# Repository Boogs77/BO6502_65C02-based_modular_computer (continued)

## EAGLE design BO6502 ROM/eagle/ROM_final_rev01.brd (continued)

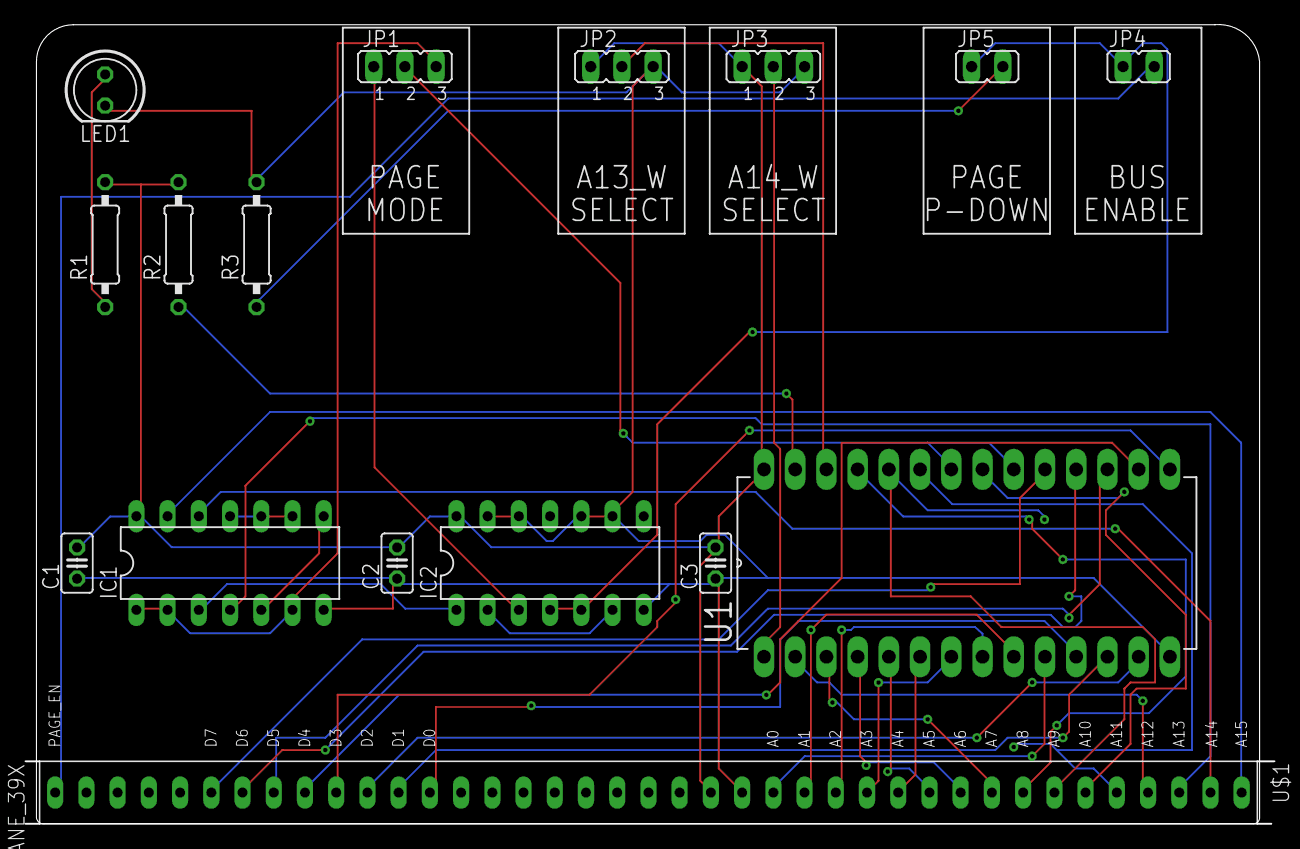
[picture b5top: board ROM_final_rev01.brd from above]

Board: 2 copper layers, 101.6 x 65.0 mm, 16 parts (0 on the bottom side), 40 nets.

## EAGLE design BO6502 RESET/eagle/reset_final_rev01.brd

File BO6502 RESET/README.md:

# BO6502 Reset & Clock Module

The **Reset & Clock Module** is a critical system utility for the BO6502. It provides a reliable power-on reset pulse and a flexible clock generation system to adapt the CPU speed to different hardware requirements.

---

## 🛠 Hardware Specifications

This module combines two essential system functions: power management and timing.

### Reset Circuitry
* **Logic:** Built around the classic **NE555** timer configured in monostable mode.
* **Function:** Ensures a clean and stable active-low RESET pulse upon power-up or manual trigger, ensuring the 65C02 CPU and peripherals initialize correctly.

### Clock Management & Scaling
The board features a flexible clock distribution system, allowing the user to select between different frequencies using a **74LS74** dual flip-flop for frequency division.

* **Direct 2 MHz Clock:** The system can be driven directly by a 2 MHz source (Note: the onboard clock on the CPU module must be disabled when using this configuration).
* **Scaled Frequencies:** Using the 7474 divider, the module can provide:
    * **1 MHz** (Division by 2).
    * **500 kHz** (Further division).
* **Selection:** This allows for high-speed operation or lower speeds for debugging and compatibility with older peripherals.

---

## 🕹️ Integration & Configuration

To use the external clock from this module, ensure the clock jumper/oscillator on the **BO6502 CPU Module** is disconnected to avoid bus contention.

| Frequency | Source / Logic | Recommended Use |
| :--- | :--- | :--- |
| **2 MHz** | Direct Bypass | Standard high-speed operation |
| **1 MHz** | 7474 Divider (Q1) | Standard 6502 compatibility |
| **500 kHz** | 7474 Divider (Q2) | Debugging / Slow peripheral testing |

---

## 📐 Board Layout & Rendering

The layout provides easy access to the reset button and features jumpers for quick frequency switching.

---

## 📂 Related Modules
* 🧠 **[CPU Module](https://github.com/Boogs77/BO6502/blob/main/BO6502%20CPU/README.md)**: W65C02 central processor (requires clock coordination).
* 🏗️ **[Backplate System](https://github.com/Boogs77/BO6502/blob/main/BO6502%20BACKPLATE/README.md)**: Distributes the Reset and Clock signals to all slots.
* 🖥️ **[Monitor Interface](https://github.com/Boogs77/BO6502/blob/main/BO6502%20MONITOR/README.md)**: Used to verify bus activity after a reset.

---

## 🏭 Gerber files

Ready for PCB manufacturing (2 layers, drill file included). The drill hits of each file have been checked against its EAGLE board.

| Gerber (ZIP) | Exported from |
| :--- | :--- |
| [`BO6502_reset_gerber.zip`](export/BO6502_reset_gerber.zip) | `reset_final_rev01.brd` |

---
© 2026 Boogs77 | BO6502 Project - Technical Documentation.

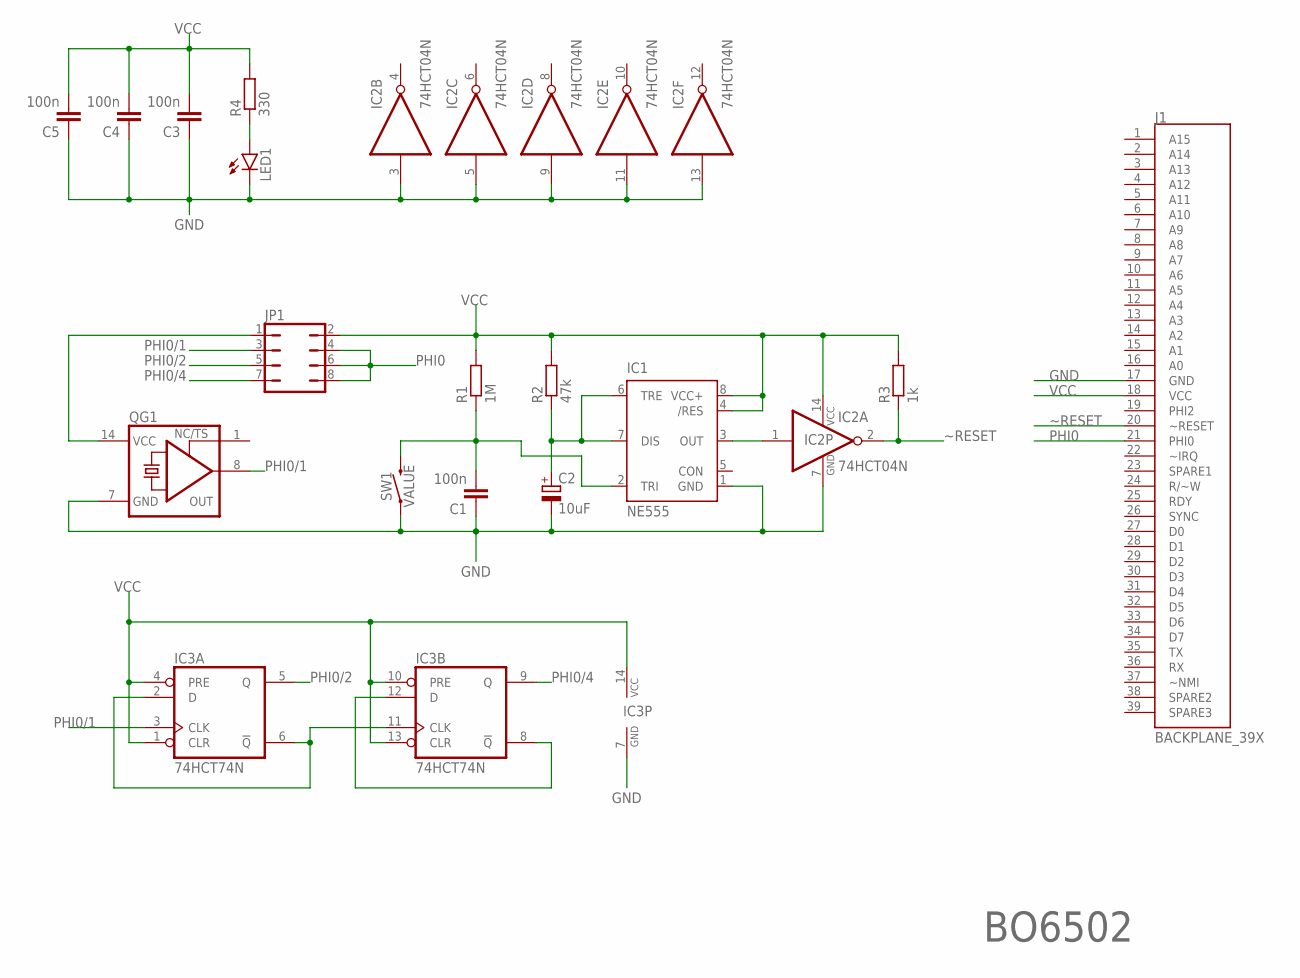
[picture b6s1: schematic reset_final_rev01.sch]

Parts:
C1, C3, C4, C5: 100n; C025-025X050
C2: 10uF; B45181A
IC1: NE555; DIL-08
IC2: 74HCT04N; DIL14
IC3: 74HCT74N; DIL14
J1: BACKPLANE_39X; BP_39X
JP1: JP4Q
LED1: LED5MM
QG1: XO-14; DIL14S
R1: 1M; 0207/10
R2: 47k; 0207/10
R3: 1k; 0207/10
R4: 330; 0207/10
SW1: MOMENTARY-SWITCH-SPST-PTH-6.0MM-KIT; TACTILE_SWITCH_PTH_6.0MM_KIT

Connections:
GND: C1.1, C2.-, C3.1, C4.1, C5.1, IC1.1 (GND), IC2.3 (I), IC2.5 (I), IC2.7 (GND), IC2.9 (I), IC2.11 (I), IC2.13 (I), IC3.7 (GND), J1.17 (GND), LED1.K (C), QG1.7 (GND), SW1.1
unnamed: JP1.1, QG1.14 (VCC)
unnamed: IC1.3 (OUT), IC2.1 (I)
unnamed: C2.+, IC1.6 (TRE), IC1.7 (DIS), R2.1
unnamed: C1.2, IC1.2 (TRI), R1.1, SW1.3 (2)
unnamed: LED1.A, R4.1
unnamed: IC3.2 (D), IC3.6 (!Q), IC3.11 (CLK)
unnamed: IC3.8 (!Q), IC3.12 (D)
PHI0: J1.21 (PHI0), JP1.4, JP1.6, JP1.8
PHI0/1: IC3.3 (CLK), JP1.3, QG1.8 (OUT)
PHI0/2: IC3.5 (Q), JP1.5
PHI0/4: IC3.9 (Q), JP1.7
VCC: C3.2, C4.2, C5.2, IC1.4 (/RES), IC1.8 (VCC+), IC2.14 (VCC), IC3.1 (CLR), IC3.4 (PRE), IC3.10 (PRE), IC3.13 (CLR), IC3.14 (VCC), J1.18 (VCC), JP1.2, R1.2, R2.2, R3.2, R4.2
~RESET: IC2.2 (O), J1.20 (~RESET), R3.1

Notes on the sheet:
BO6502

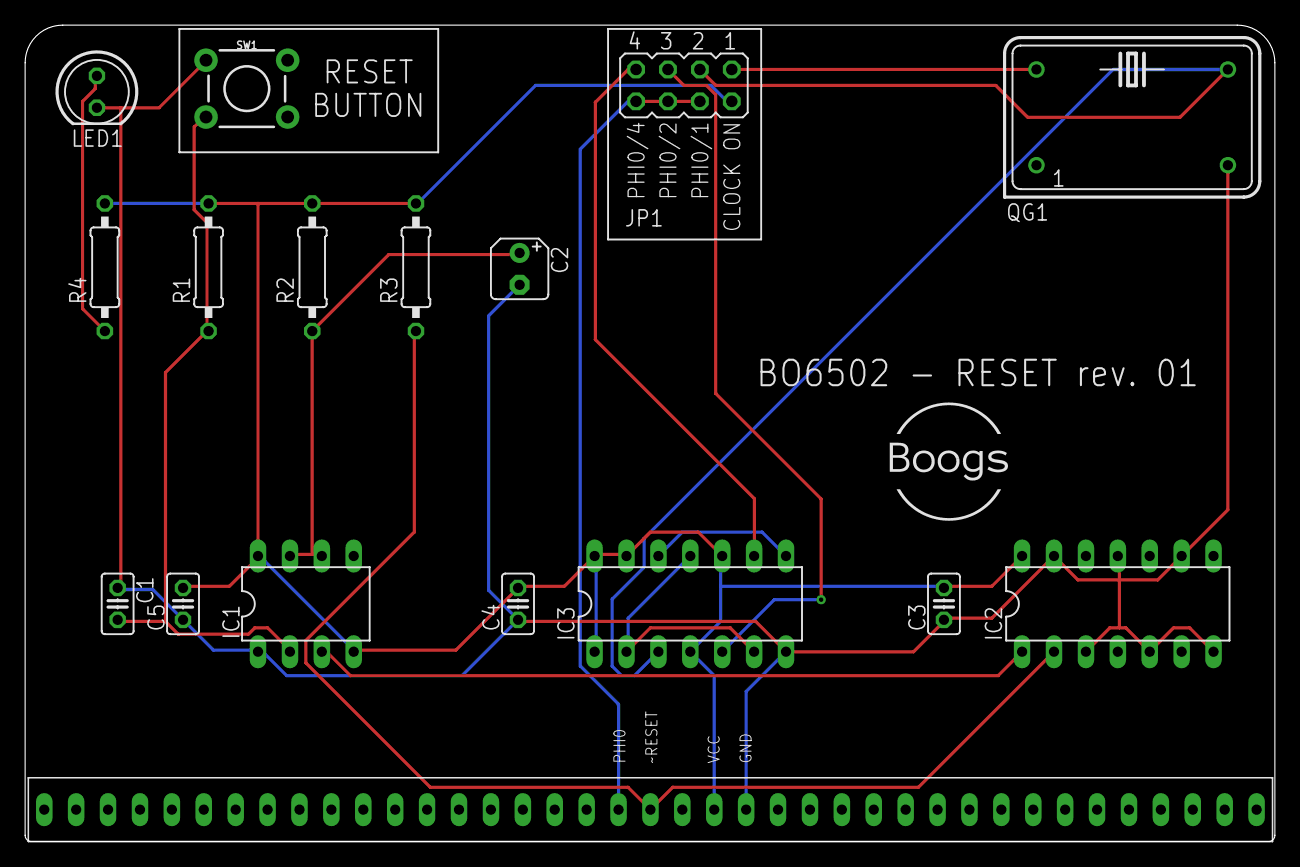
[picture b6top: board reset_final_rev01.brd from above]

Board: 2 copper layers, 99.5 x 65.0 mm, 17 parts (0 on the bottom side), 14 nets.

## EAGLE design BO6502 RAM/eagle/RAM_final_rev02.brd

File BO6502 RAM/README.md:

# BO6502 RAM Module

The **RAM Module** provides the primary volatile memory storage for the BO6502 system. This revision features a highly flexible addressing logic, allowing the user to map or exclude specific memory banks through a series of onboard jumpers.

---

## 🛠 Hardware Specifications

The module is designed to interface with the 6502 bus, providing fast access to 32KB of static RAM (SRAM).

* **Base Addressing:** By default, the module is mapped to the **$0000 - $7FFF** range. This is achieved by connecting the **A15** address line to the Enable pin of the decoder logic (active when A15 is Low).
* **Clock Synchronization:** The module typically triggers with the system clock to ensure data integrity during R/W cycles. However, **JP4** allows the user to set **IC2** as "Always Enabled," bypassing the system clock trigger for specific hardware configurations.

---

## 🕹️ Jumper Configuration & Memory Mapping

This module stands out for its versatility, managed through several jumper sets:

### I/O Exclusion Jumpers
The board includes **8 dedicated jumpers** designed to "carve out" space within the $0000 - $7FFF range. This allows other peripherals (such as I/O modules) to reside in that memory space without causing bus contention with the RAM.

### Address Bank Management
* **JP1 & JP2:** These jumpers allow the physical disconnection of **A13** and **A14** lines, useful for testing or specific memory mirroring configurations.
* **High-Memory Toggle:** A specific jumper configuration allows the RAM to be remapped to the **$8000 - $FFFF** range (High Memory) instead of its default Low Memory position.

---

## 📐 Board Layout & Rendering

The Revision 02 layout features optimized traces for high-speed signal integrity and clearly labeled jumper blocks for easy configuration.

---

## 📂 Related Modules
* 🏗️ **[Backplate System](https://github.com/Boogs77/BO6502/blob/main/BO6502%20BACKPLATE/README.md)**: 39-pin system bus connection.
* 🧠 **[CPU Module](https://github.com/Boogs77/BO6502/blob/main/BO6502%20CPU/README.md)**: W65C02 central processor.
* 🖥️ **[Monitor Interface](https://github.com/Boogs77/BO6502/blob/main/BO6502%20MONITOR/README.md)**: Recommended for debugging RAM read/write operations.

---

## 🏭 Gerber files

Ready for PCB manufacturing (2 layers, drill file included). The drill hits of each file have been checked against its EAGLE board.

| Gerber (ZIP) | Exported from |
| :--- | :--- |
| [`BO6502-RAM_gerber.zip`](export/BO6502-RAM_gerber.zip) | `RAM_final_rev02.brd` |

---
© 2026 Boogs77 | BO6502 Project - Technical Documentation.

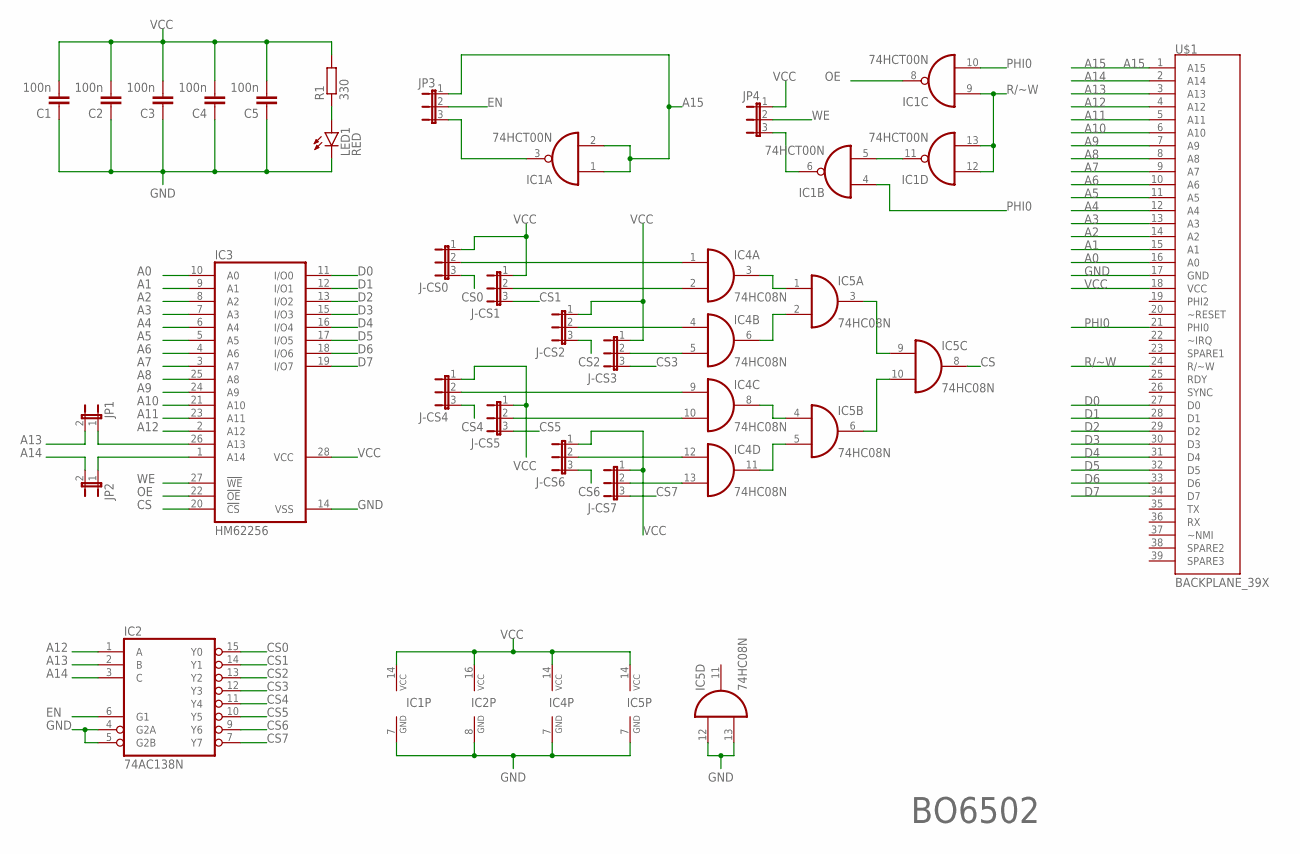
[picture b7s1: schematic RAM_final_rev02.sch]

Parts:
C1, C2, C3, C4, C5: 100n; C025-025X050
IC1: 74HCT00N; DIL14
IC2: 74AC138N; DIL16
IC3: HM62256; DIL28-6
IC4, IC5: 74HC08N; DIL14
J-CS0: J-CS0; JP2
J-CS1: J-CS1; JP2
J-CS2: J-CS2; JP2
J-CS3: J-CS3; JP2
J-CS4: J-CS4; JP2
J-CS5: J-CS5; JP2
J-CS6: J-CS6; JP2
J-CS7: J-CS7; JP2
JP1: JP1
JP2: JP2; JP1
JP3: JP3; JP2
JP4: JP4; JP2
LED1: RED; LED5MM
R1: 330; 0207/10
U$1: BACKPLANE_39X; BP_39X

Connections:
A0: IC3.10 (A0), U$1.16 (A0)
A1: IC3.9 (A1), U$1.15 (A1)
A2: IC3.8 (A2), U$1.14 (A2)
A3: IC3.7 (A3), U$1.13 (A3)
A4: IC3.6 (A4), U$1.12 (A4)
A5: IC3.5 (A5), U$1.11 (A5)
A6: IC3.4 (A6), U$1.10 (A6)
A7: IC3.3 (A7), U$1.9 (A7)
A8: IC3.25 (A8), U$1.8 (A8)
A9: IC3.24 (A9), U$1.7 (A9)
A10: IC3.21 (A10), U$1.6 (A10)
A11: IC3.23 (A11), U$1.5 (A11)
A12: IC2.1 (A), IC3.2 (A12), U$1.4 (A12)
A13: IC2.2 (B), JP1.2, U$1.3 (A13)
A14: IC2.3 (C), JP2.2, U$1.2 (A14)
A15: IC1.1 (I0), IC1.2 (I1), JP3.1, U$1.1 (A15)
CS: IC3.20 (!CS), IC5.8 (O)
CS0: IC2.15 (Y0), J-CS0.3
CS1: IC2.14 (Y1), J-CS1.3
CS2: IC2.13 (Y2), J-CS2.3
CS3: IC2.12 (Y3), J-CS3.3
CS4: IC2.11 (Y4), J-CS4.3
CS5: IC2.10 (Y5), J-CS5.3
CS6: IC2.9 (Y6), J-CS6.3
CS7: IC2.7 (Y7), J-CS7.3
D0: IC3.11 (I/O0), U$1.27 (D0)
D1: IC3.12 (I/O1), U$1.28 (D1)
D2: IC3.13 (I/O2), U$1.29 (D2)
D3: IC3.15 (I/O3), U$1.30 (D3)
D4: IC3.16 (I/O4), U$1.31 (D4)
D5: IC3.17 (I/O5), U$1.32 (D5)
D6: IC3.18 (I/O6), U$1.33 (D6)
D7: IC3.19 (I/O7), U$1.34 (D7)
EN: IC2.6 (G1), JP3.2
GND: C1.1, C2.1, C3.1, C4.1, C5.1, IC1.7 (GND), IC2.4 (G2A), IC2.5 (G2B), IC2.8 (GND), IC3.14 (VSS), IC4.7 (GND), IC5.7 (GND), IC5.12 (I0), IC5.13 (I1), LED1.K (C), U$1.17 (GND)
unnamed: IC3.26 (A13), JP1.1
unnamed: IC1.5 (I1), IC1.11 (O)
unnamed: IC1.3 (O), JP3.3
unnamed: IC1.6 (O), JP4.3
unnamed: IC4.3 (O), IC5.1 (I0)
unnamed: LED1.A, R1.1
unnamed: IC4.6 (O), IC5.2 (I1)
unnamed: IC4.8 (O), IC5.4 (I0)
unnamed: IC3.1 (A14), JP2.1
unnamed: IC4.11 (O), IC5.5 (I1)
unnamed: IC5.3 (O), IC5.9 (I0)
unnamed: IC5.6 (O), IC5.10 (I1)
unnamed: IC4.1 (I0), J-CS0.2
unnamed: IC4.2 (I1), J-CS1.2
unnamed: IC4.4 (I0), J-CS2.2
unnamed: IC4.5 (I1), J-CS3.2
unnamed: IC4.9 (I0), J-CS4.2
unnamed: IC4.10 (I1), J-CS5.2
unnamed: IC4.12 (I0), J-CS6.2
unnamed: IC4.13 (I1), J-CS7.2
OE: IC1.8 (O), IC3.22 (!OE)
PHI0: IC1.4 (I0), IC1.10 (I1), U$1.21 (PHI0)
R/~W: IC1.9 (I0), IC1.12 (I0), IC1.13 (I1), U$1.24 (R/~W)
VCC: C1.2, C2.2, C3.2, C4.2, C5.2, IC1.14 (VCC), IC2.16 (VCC), IC3.28 (VCC), IC4.14 (VCC), IC5.14 (VCC), J-CS0.1, J-CS1.1, J-CS2.1, J-CS3.1, J-CS4.1, J-CS5.1, J-CS6.1, J-CS7.1, JP4.1, R1.2, U$1.18 (VCC)
WE: IC3.27 (!WE), JP4.2

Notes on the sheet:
BO6502

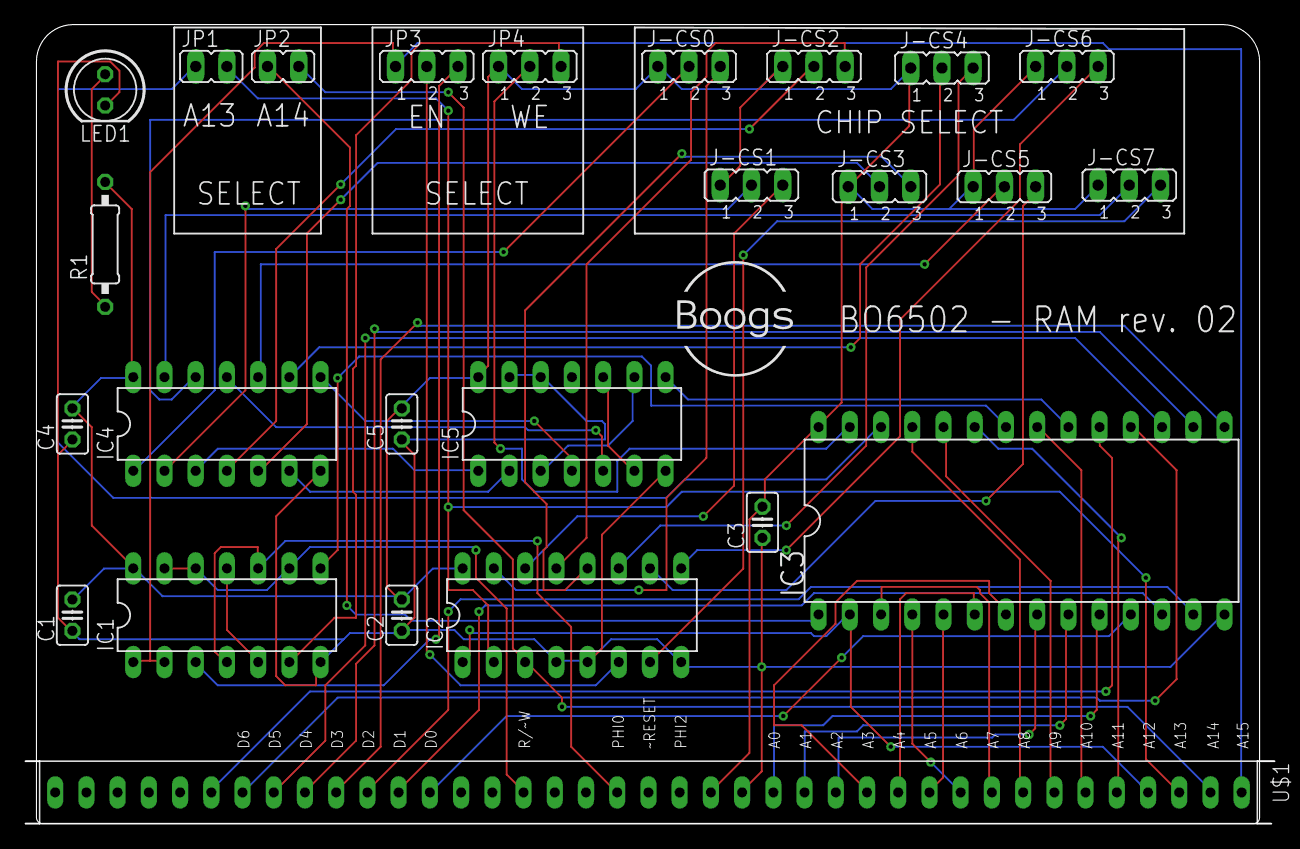
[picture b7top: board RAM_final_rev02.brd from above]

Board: 2 copper layers, 101.6 x 65.0 mm, 25 parts (0 on the bottom side), 60 nets.

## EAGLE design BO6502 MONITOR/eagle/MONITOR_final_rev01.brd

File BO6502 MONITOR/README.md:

# BO6502 Monitor Interface

The **Monitor Interface** is a diagnostic tool designed to provide real-time visibility into the internal operations of the BO6502 system. By interfacing an **Arduino Mega**, it allows the user to inspect the Address Bus and Data Bus during execution.

---

## 🛠 Operation & Hardware Setup

This module is specifically conceived for debugging at very low clock frequencies (manual pulsing or slow-stepping). It is designed to work in conjunction with an external clock source, such as the **[6502 Clock Module by dbuchewald](https://github.com/dbwald/6502/tree/master/Schematics/Clock_module)**.

* **Controller:** The board features a socket for an **Arduino Mega**, which acts as the logic analyzer.
* **Bus Monitoring:** It captures the state of the 16-bit Address Bus and the 8-bit Data Bus.
* **Triggering:** The monitoring logic is synchronized with the system clock signal connected to an Arduino interrupt pin.
* **Power Management:** A **dedicated jumper** has been included in the design. This allows the user to choose whether to power the Arduino Mega from the system bus or to isolate it when using an **external power source**, preventing potential power conflicts.

---

## 💻 Logic & Firmware

The monitoring principle follows the implementation popularized by **Ben Eater**. The firmware triggers a read cycle on every **rising edge** of the clock.

* **Firmware Reference:** **[6502-monitor.ino](https://eater.net/downloads/6502-monitor.ino)**.
* **Mechanism:** When the clock signal goes high, the Arduino triggers an interrupt service routine (ISR) to sample the address and data lines instantly, formatting the output for the Serial Monitor (Hexadecimal/Binary).

---

## 🕹️ Addressing & Compatibility

Since this module acts as a passive listener (sniffer) on the bus, it does not require a specific I/O address range (like $DXXX) and does not interfere with the system's memory mapping.

> [!IMPORTANT]
> This module is intended for **low-speed diagnostics only**. Due to the sampling latency of the Arduino Mega, it cannot monitor the bus accurately at the full 1MHz+ speeds of the 65C02.

---

## 📐 Board Layout & Rendering

The board provides clean routing for the 39-pin system bus directly to the Arduino Mega digital headers.

---

## 📂 Related Modules
* 🏗️ **[Backplate System](https://github.com/Boogs77/BO6502/blob/main/BO6502%20BACKPLATE/README.md)**: Main 39-pin system bus connection.
* 🧠 **[CPU Module](https://github.com/Boogs77/BO6502/blob/main/BO6502%20CPU/README.md)**: W65C02 central processor.
* 🔴 **[LED Test Board](https://github.com/Boogs77/BO6502/blob/main/BO6502%20LED/README.md)**: Alternative visual diagnostic tool.

---

## 🏭 Gerber files

Ready for PCB manufacturing (2 layers, drill file included). The drill hits of each file have been checked against its EAGLE board.

| Gerber (ZIP) | Exported from |
| :--- | :--- |
| [`BO6502_MONITOR_gerber.zip`](export/BO6502_MONITOR_gerber.zip) | `MONITOR_final_rev01.brd` |

---
© 2026 Boogs77 | BO6502 Project - Technical Documentation.

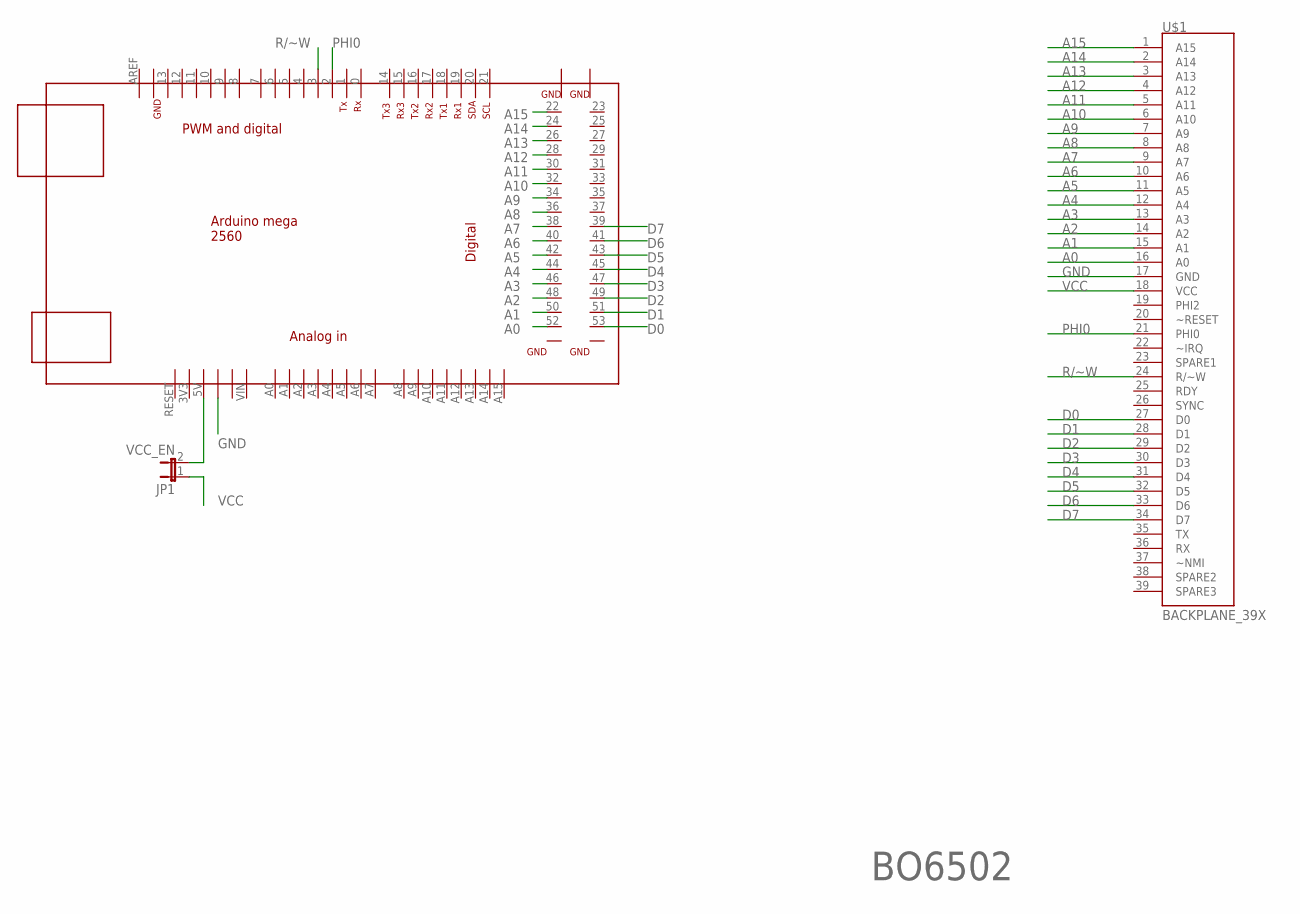
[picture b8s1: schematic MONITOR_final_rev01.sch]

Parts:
JP1: VCC_EN; JP1
U$1: BACKPLANE_39X; BP_39X
U$2: MEGA_DEVICE; MEGAOUTLINE

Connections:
A0: U$1.16 (A0), U$2.52
A1: U$1.15 (A1), U$2.50
A2: U$1.14 (A2), U$2.48
A3: U$1.13 (A3), U$2.46
A4: U$1.12 (A4), U$2.44
A5: U$1.11 (A5), U$2.42
A6: U$1.10 (A6), U$2.40
A7: U$1.9 (A7), U$2.38
A8: U$1.8 (A8), U$2.36
A9: U$1.7 (A9), U$2.34
A10: U$1.6 (A10), U$2.32
A11: U$1.5 (A11), U$2.30
A12: U$1.4 (A12), U$2.28
A13: U$1.3 (A13), U$2.26
A14: U$1.2 (A14), U$2.24
A15: U$1.1 (A15), U$2.22
D0: U$1.27 (D0), U$2.53
D1: U$1.28 (D1), U$2.51
D2: U$1.29 (D2), U$2.49
D3: U$1.30 (D3), U$2.47
D4: U$1.31 (D4), U$2.45
D5: U$1.32 (D5), U$2.43
D6: U$1.33 (D6), U$2.41
D7: U$1.34 (D7), U$2.39
GND: U$1.17 (GND), U$2.GND@2 (GND)
unnamed: JP1.2, U$2.5V
PHI0: U$1.21 (PHI0), U$2.2
R/~W: U$1.24 (R/~W), U$2.3
VCC: JP1.1, U$1.18 (VCC)

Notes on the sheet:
BO6502

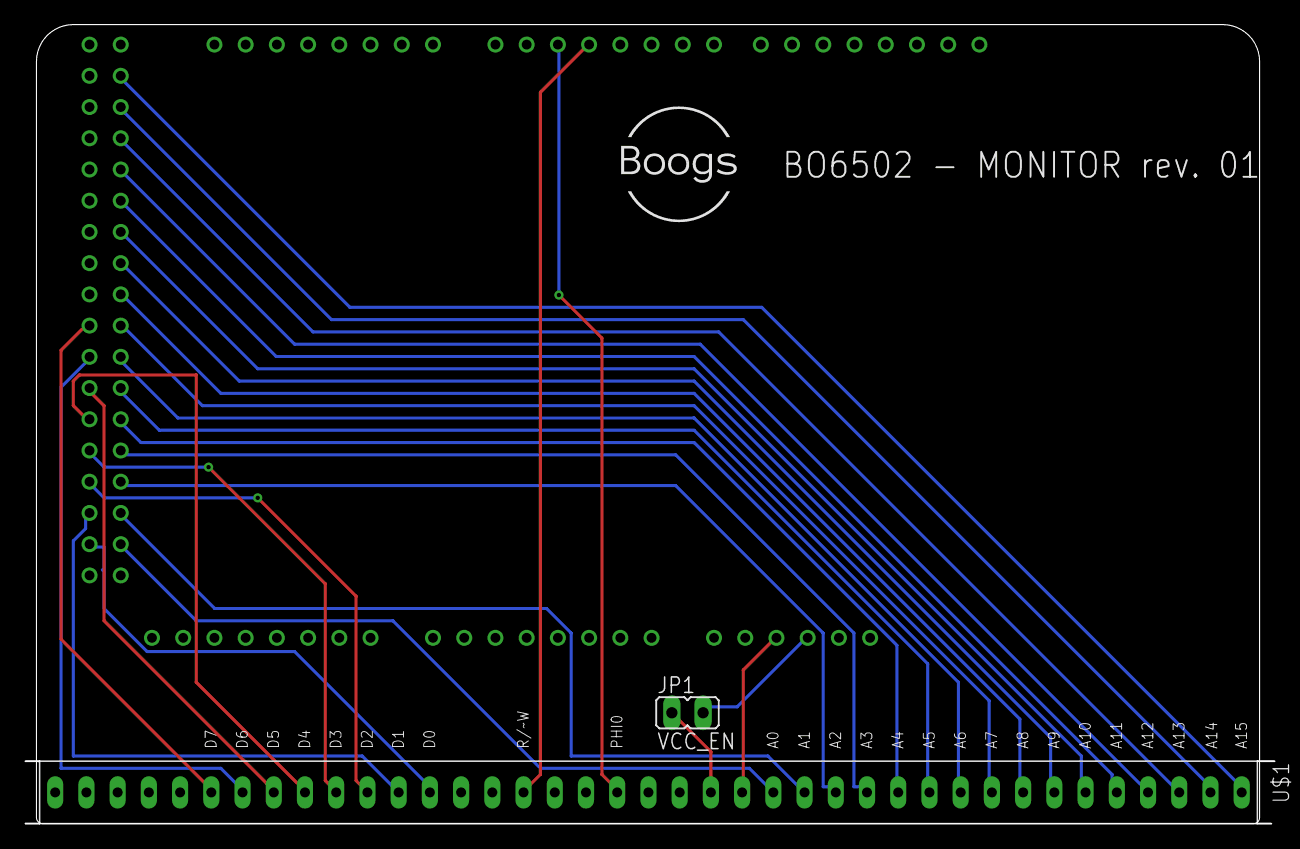
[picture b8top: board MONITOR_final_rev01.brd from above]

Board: 2 copper layers, 101.6 x 65.0 mm, 3 parts (1 on the bottom side), 29 nets.

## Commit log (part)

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2026-01-30 move
2026-01-31 picture changes
2026-01-31 Add README for BO6502 backplate
2026-01-31 Add backplate_final_rev02 section to README
2026-01-31 Update backplate_final_rev02 formatting in README
2026-01-31 Update README to clarify voltage regulator details
2026-01-31 Update README with backplate details and formatting
    Corrected formatting and added details about backplate revisions.
2026-01-31 few changes
2026-01-31 main changes
2026-02-01 many changes
2026-02-01 Changes images pcb color
2026-02-01 Audio changes
2026-02-01 change name
2026-02-01 Add KEYB PCB
2026-02-01 Rename readme.MD to README.md
2026-02-01 PCB LEDs changes
2026-02-01 Add monitor PCB
2026-02-01 add RAM PCB
2026-02-01 Add RESET PCB
2026-02-01 add rom PCBs
2026-02-02 add SDCard PCB
2026-02-02 add SERIAL PCB
2026-02-02 add VDU PCB
2026-02-02 final README.md
2026-05-17 Update README to remove citation markers
    Removed citation markers from the technical overview.
2026-05-17 Remove citation markers from README.md
